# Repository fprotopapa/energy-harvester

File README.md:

# Energy-harvester

## Description

Energy harvester for Peltier elements with an output voltage of 3.3V. 
One-sided design optimized for home manufacturing.

## ToDo

- [x] Check footprints
- [x] Make BOM 
- [x] Check schematic

## PCB

## BOM

|# |Designator	|Part #	|Mfr.	|Description |Footprint	|Qty. |
|- |----------- |------ |---- |----------- |--------- |---- |
|1 |C4	|0805ZC105JAT2A|	Kyocera AVX	|10V 1uF	|0805 (2012 mm)	|1|
|2	|C1	|0805ZD106MAT2A|	Kyocera AVX	|10V 10uF	|0805(2012 mm)	|1|
|3	|C5|	0805ZD475KAT4A|	Kyocera AVX|	10V 4.7uF|	0805 (2012 mm)	|1|
|4	|C2, C3|	0805ZC102KAT2A|	Kyocera AVX|	10V 1nF|	0805 (2012 mm)	|2|
|5	|R1|	RCV08051M00JNEA|	Vishay|	1/8W 1MR|	0805 (2012 mm) |1|
|6	|R2|	CRCW0805100RJNEB|	Vishay|	1/8W 100R|	0805 (2012 mm) |1|
|7	|IC1|	LTC3108EGN#TRPBF|	Analog Devices|	LTC3108|	SSOP-16	|1|
|8	|L1|	WE-EHPI 74488540070|	Wuerth|	Ratio 1:100 coupled inductors|	SMD	|1|
|9	|Q1|	RUM002N02|	Rohm|	Mosfet N-Channel|	SOT-723-3	|1|

## KiCAD

``` KiCAD v5.99 ```

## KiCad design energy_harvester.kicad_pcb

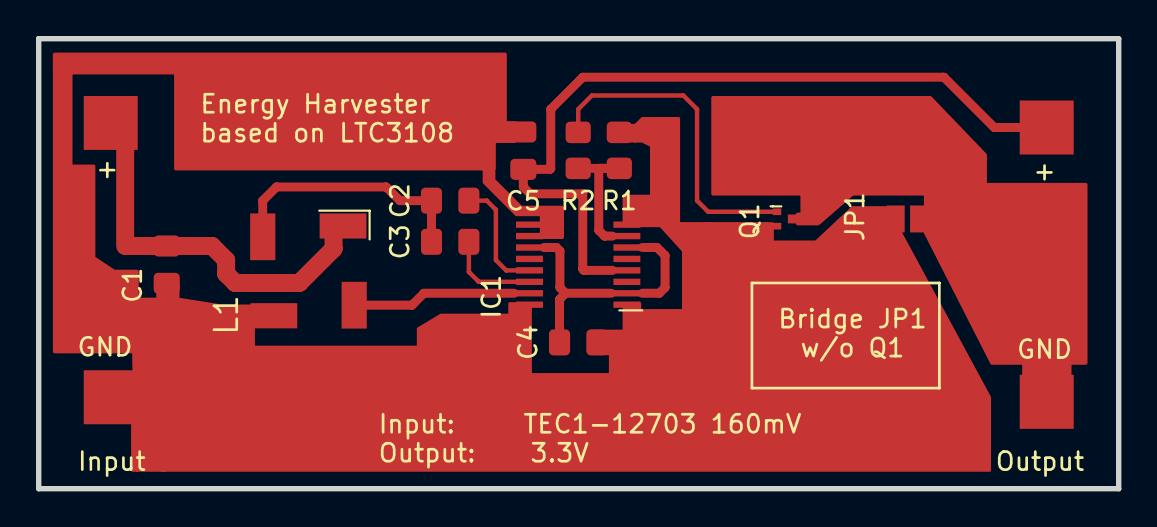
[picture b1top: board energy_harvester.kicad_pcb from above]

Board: 2 copper layers, 60.0 x 25.0 mm, 13 parts (0 on the bottom side), 11 nets.

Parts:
C1: 10u; C_0805_2012Metric_Pad1.18x1.45mm_HandSolder
C2: 1n; C_0805_2012Metric_Pad1.18x1.45mm_HandSolder
C3: 990p; C_0805_2012Metric_Pad1.18x1.45mm_HandSolder
C4: 1u; C_0805_2012Metric_Pad1.18x1.45mm_HandSolder
C5: 5u; C_0805_2012Metric_Pad1.18x1.45mm_HandSolder
IC1: LTC3108EGN-1-PBF
J1, J2: Conn_01x02_Female; 2-pad
JP1: Jumper_2_Bridged; SolderJumper-2_P1.3mm_Open_Pad1.0x1.5mm
L1: 74488540070
Q1: RUM002N02T2L; SOTFL40P120X55-3N
R1: 1M; R_0805_2012Metric_Pad1.20x1.40mm_HandSolder
R2: 100; R_0805_2012Metric_Pad1.20x1.40mm_HandSolder

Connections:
/C1: C2.2, IC1.13 (C1)
/C2: C3.2, IC1.14 (C2)
/PGD: IC1.7 (PGD), R1.1, R2.1
/SW: IC1.15 (SW), L1.2
/VAUX: C4.1, IC1.2 (VAUX), IC1.6 (VLDO), IC1.11 (VS1)
/VOUT: C5.1, IC1.4 (VOUT), J2.1
GND: C1.2, C4.2, C5.2, IC1.1 (GND), IC1.8 (GND), IC1.9 (GND), IC1.10 (VS2), IC1.16 (GND), J1.1, JP1.2 (B), L1.3, Q1.2, R1.2
unnamed: C1.1, J1.2, L1.1
unnamed: C2.1, C3.1, L1.4
unnamed: J2.2, JP1.1 (A), Q1.3
unnamed: Q1.1, R2.2

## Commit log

2021-12-01 Add traces, step files, corr in schematic
2021-12-01 Update gitignore
2021-12-01 Add silkscreen desc
2021-12-01 Add 3D image
2021-12-01 Add ToDo
2021-12-01 Add Silkscreen
2021-12-01 Add BOM
2021-12-01 Change C value
2021-12-01 Add MOSFET
2021-12-01 Change C4
2021-12-01 Update footprints
2021-12-01 Update image
2021-12-01 Change C4 & update ToDo
2021-12-01 Change thickness L1
2022-04-28 ignore zip
2022-04-28 Pour Ground
